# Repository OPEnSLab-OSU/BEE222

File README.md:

# BEE222
Course code, PCB design files

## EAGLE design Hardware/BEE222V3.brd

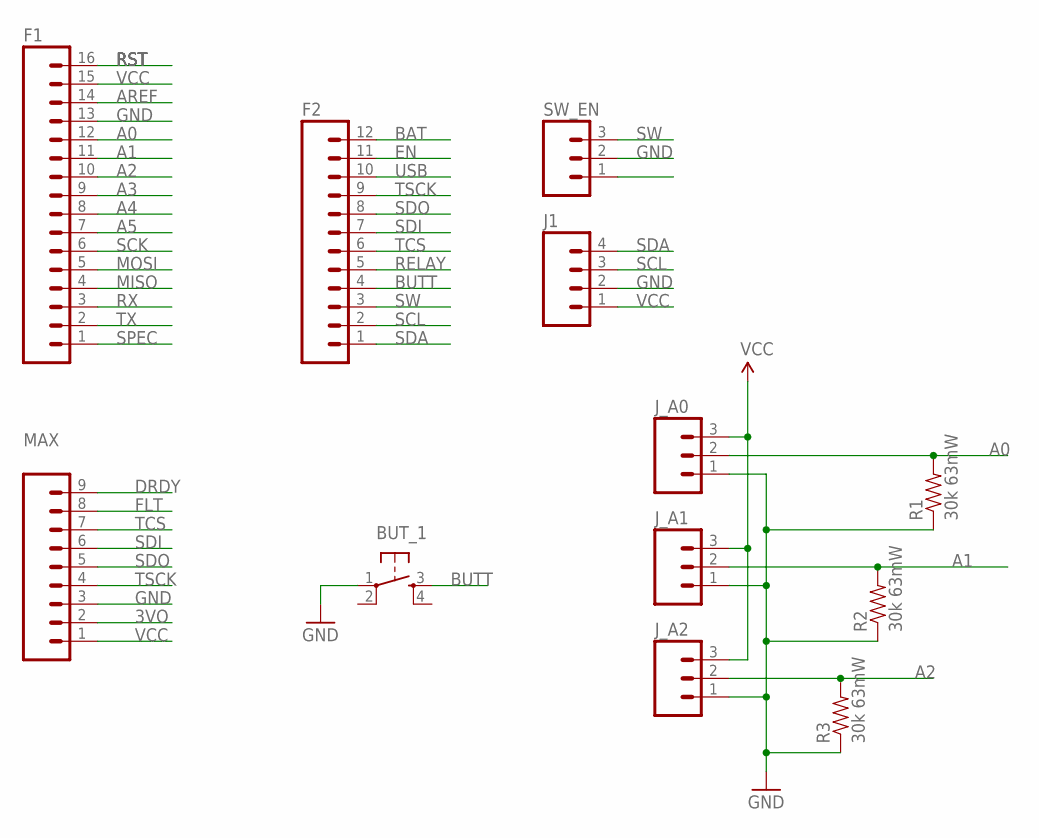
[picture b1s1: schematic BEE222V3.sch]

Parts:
BUT_1: TAC_SWITCHPTH; TACTILE-PTH
F1: M16PTH; 1X16
F2: M12PTH; 1X12
J1: M04PTH; 1X04
J_A0, J_A1, J_A2: M03JST-PTH-VERT; JST-3-PTH-VERT
MAX: M09; 1X09
R1, R2, R3: 30k 63mW; 1206
SW_EN: M03PTH; 1X03

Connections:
3VO: MAX.2
A0: F1.12, J_A0.2, R1.2
A1: F1.11, J_A1.2, R2.2
A2: F1.10, J_A2.2, R3.2
A3: F1.9
A4: F1.8
A5: F1.7
AREF: F1.14
BAT: F2.12
BUTT: BUT_1.3, F2.4
DRDY: MAX.9
EN: F2.11
FLT: MAX.8
GND: BUT_1.1, F1.13, J1.2, J_A0.1, J_A1.1, J_A2.1, MAX.3, R1.1, R2.1, R3.1, SW_EN.2
MISO: F1.4
MOSI: F1.5
RELAY: F2.5
RST: F1.16
RX: F1.3
SCK: F1.6
SCL: F2.2, J1.3
SDA: F2.1, J1.4
SDI: F2.7, MAX.6
SDO: F2.8, MAX.5
SPEC: F1.1
SW: F2.3, SW_EN.3
TCS: F2.6, MAX.7
TSCK: F2.9, MAX.4
TX: F1.2
USB: F2.10
VCC: F1.15, J1.1, J_A0.3, J_A1.3, J_A2.3, MAX.1

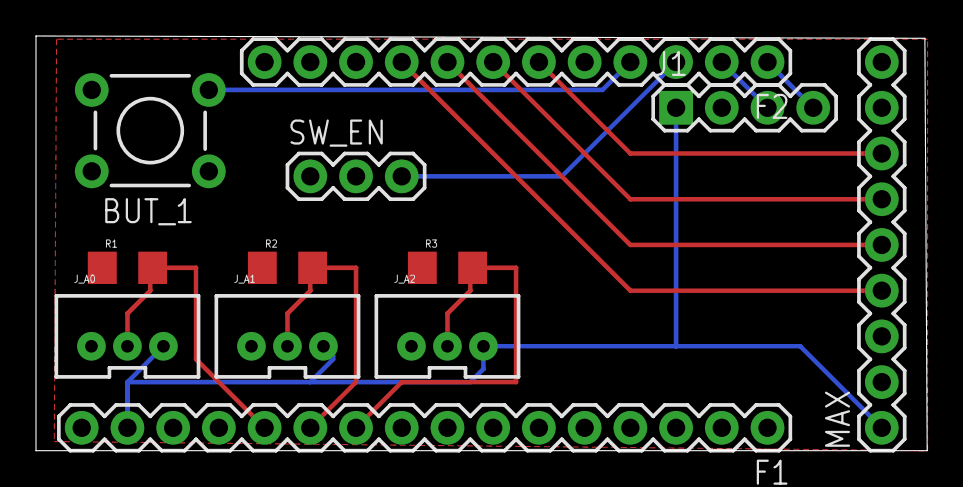
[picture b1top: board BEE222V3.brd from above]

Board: 2 copper layers, 49.5 x 23.0 mm, 12 parts (0 on the bottom side), 13 nets.

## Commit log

2019-09-18 Create HardwareReadme
2019-09-18 Latest version BEE222 board Spring'19

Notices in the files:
parts and their libraries:
SparkFun-Retired: Licensing:Creative Commons ShareAlike 4.0 International - https://creativecommons.org/licenses/by-sa/4.0
